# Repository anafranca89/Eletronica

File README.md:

# Fonte Reguladora de Tensão 

## Descrição
O projeto visava a construção de um circuito de uma fonte de tensão ajustável entre 3V
a 12V com 100mA de corrente na carga. Tendo como a tensão de entrada uma tomada de
127V.
O projeto foi simulado digitalmente no site Falstad.

[Link para o circuito no Falstad](https://tinyurl.com/2bbb4j2l)

## Circuito no  EAGLE:

Os arquivos .bdr e .sch para abertura no EAGLE estão na pasta "Arquivos_EAGLE"
bem como a  versão em PDF para impressão

## Vídeo explicando o projeto:

[Link para o vídeo](https://drive.google.com/file/d/12u-_e9nXhzFPCVaqadtqyPuUy2_YhOlK/view?usp=sharing)

## Componentes Utilizados:

| Quant. | Nome do Componente | Especificação | Valor |
|---|---|---|---|
| 1| Protoboard         | 400 pontos    | R$ 8,90 |
| 1| Ponte Refiticadora | 2W10M 2A 800V    | R$ 3,90 | 
| 1| Capacitor eletrolítico| 470uF x 50V     | R$ 1,68 |
| 1| LED difuso         | 5mm    | R$ 0,20 | 
| 2 | Resistores| 4k7 1/4W | R$ 0,90 - 10 unidades | 
| 1 | Resistor | 1k5 1/4W | R$ 0,90 - 10 unidades |
|1 | Resistor | 2W 100ohm | R$ 1,20 |
|1 | Diodo Zenner | 13V 1W | R$ 0,50 |
|1 | Potenciômetro Linear | 10k | R$ 2,20 |
|1 | Transistor NPN |  2N2222A | R$ 2,60 |
| TOTAL |--------- |--------- |R$ 22,98|

## Explicação do uso dos componentes: 

### Transformador:
Neste circuito o transformador é o componente inicial. Seu papel é transformar a tensão
de pico vinda da tomada em uma tensão menor, proporcional ao número de espiras de cada
um dos lados.
No circuito, é necessário realizar a retificação da corrente alternada vinda da tomada, que é realizado pela ponte retificadora.\
O transformador escolhido para o projeto, após essa retificação, mediu 24,2V no capacitor.
Desse modo, conseguimos calcular a proporcionalidade no número de espiras para colocar no simulador.

> Vpico = 127 * √2 ≈ 179,61 V ≈ 180 V

> Relação de espiras: 179,61 ÷ 24,2 ≈ 7,4

### Ponte Retificadora (Ponte de Diodos):
A corrente da tomada se comporta de maneira alternada, a ponte de diodo tem como objetivo direcionar o caminho da corrente em um único sentido, transformando em corrente contínua. Desse modo, é possívelaproveitar a corrente vinda de ambas as direções.\
Sabe-se também que a ponte provoca uma queda de aproximadamente 2 * 0,7V (utilizamos a ponte de silício).

### Capacitor:
O capacitor serve principalmente para armazenar energia para fornecer corrente em transientes de carga. Isso resulta em
uma tensão de saída mais estável e suave, protegendo os componentes eletrônicos sensíveis de picos de tensão e flutuações.
Para calcular a capacitância, é necessário primeiro calcular a tensão de ripple (sendo o ripple menor que 10%).\
Calculando a corrente total do circuito:

> I<sub>total</sub> = I<sub>carga</sub>+ I<sub>led</sub> + I<sub>zenner</sub> + I<sub>potenciometro</sub>\
  I<sub>total</sub> = 0,1 + 0,0045 + 0,0018 = 0,1063 A\
  C = I<sub>total</sub> / (f * V<sub>ripple</sub>)\
  Vripple = 0.1 * 24,2V = 2,42V \
  C = 0.1 / (2 * 60 * 2,4 ) = 347,22 μF
  
  Onde I é a corrente, f a frequência e V<sub>ripple</sub> a tensão de ripple.

Desse modo, para respeitar um ripple menor que 10%, era necessário pegar um capacitor com capacitância maior que 347,22 μF. Assim, escolhemos o de 470 μF (fácil de se
encontrar comercialmente e um membro do grupo já o tinha).

### Diodo Zenner:
O diodo zenner tem como função limitar a tensão que sairá do circuito para até 12V.\
Desse modo, utilizamos o diodo zenner de 13V que possibilita esta limitação de tensão, permitindo chegar ao resultado desejado (de 3 a 12V) no final do circuito.

### Potênciometro:
O potenciômetro é o componente do circuito capaz de modificar sua resistência interna.Desse modo, seu papel é poder ajustar a tensão de saída do circuito à medida que alteramos a sua resistência.

### Transistor: 
O transistor é o componente que faz com que uma mudança na carga não altere resto do circuito.

### Resistores:
Os resistores ligados ao led, ao diodo zenner, ao potenciômetro e ao transistor foram escolhidos de modo a respeitar a corrente máxima suportada por eles (segundo as especificações). Assim, pegamos os que tínhamos disponíveis e verificamos se essa corrente máxima era respeitada.

## Imagens do Projeto:

\

## Membros do Grupo:
- Ana Julia França<br>
- Maria Fernanda Maia <br>
- Pedro Otavio

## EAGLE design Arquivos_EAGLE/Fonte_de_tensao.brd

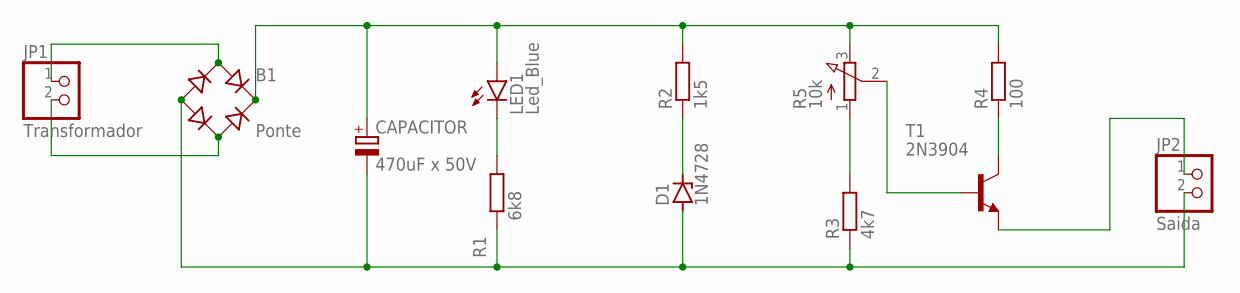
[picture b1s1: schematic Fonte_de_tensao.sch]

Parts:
B1: Ponte; RB1A
CAPACITOR: 470uF x 50V; E5-10,5
D1: 1N4728; DO41Z10
JP1: Transformador; 1X02
JP2: Saida; 1X02
LED1: Led_Blue; LED5MM
R1: 6k8; 0204/7
R2: 1k5; 0204/7
R3: 4k7; 0204/7
R4: 100; 0207/10
R5: 10k; 3RP/1610N
T1: 2N3904; TO92

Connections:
unnamed: B1.AC2, JP1.2
unnamed: B1.+, CAPACITOR.+, LED1.A, R2.2, R4.2, R5.3 (E)
unnamed: LED1.K (C), R1.2
unnamed: D1.C, R2.1
unnamed: R3.2, R5.1 (A)
unnamed: R5.2 (S), T1.2 (B)
unnamed: JP2.1, T1.3 (E)
unnamed: R4.1, T1.1 (C)
SAIDA: B1.-, CAPACITOR.-, D1.A, JP2.2, R1.1, R3.1
TRANSFORMADOR: B1.AC1, JP1.1

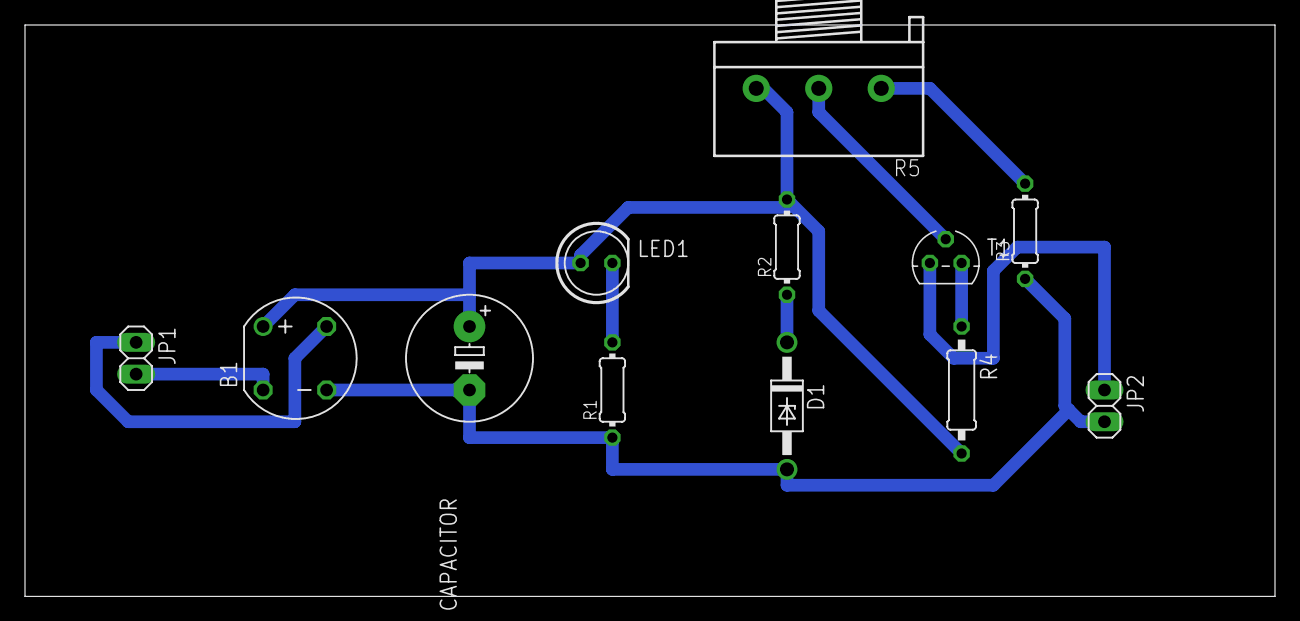
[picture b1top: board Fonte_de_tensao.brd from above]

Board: 2 copper layers, 100.0 x 45.7 mm, 12 parts (0 on the bottom side), 10 nets.

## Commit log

2025-06-28 Update README.md
    Adicionado descrição do projeto e componentes
2025-06-28 Create imges
2025-06-28 Create imge
2025-06-28 Rename Fonte_de_tensao.pdf to Circuito_para_impressão.pdf
2025-06-28 Rename Fonte_de_tensao.brd to Circuito.brd
2025-06-28 Rename Fonte_de_tensao.sch to Esquemático.sch
2025-06-30 Update README.md
    Adiciona o código do arduino
2025-06-30 Update README.md
    código do arduino
2025-06-30 Add files via upload
    adicionar imagens do circuito
2025-06-30 Update README.md
    Adicionado as imagens e o vídeo
2025-06-30 Update README.md
    Adicionando imagens e o link para o vídeo
2025-07-01 Update README.md
    membros do grupo
